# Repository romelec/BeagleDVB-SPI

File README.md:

BeagleDVB-SPI is a DVB-SPI interface on the BeagleBone Black to record/analyze TS streams.

This project is based on [BeagleLogic](https://github.com/abhishek-kakkar/BeagleLogic)

It uses the Programmable Real-Time units and matching firmware and Linux kernel modules on the
BeagleBone Black.

This is a work in progress, it kinda works but misses some data.

Directories:

* firmware: PRU Firmware
* kernel: Device Tree overlay source and kernel module source and Makefile.
* cape: The cape design files done with KiCAD

* parsing: An application to get the data and parse it to have usable TS stream
2 parameters: in and out file, generally /dev/beagledvbspi and the ouput ts file

License
--------

 * **PRU firmware & Device tree overlay** : GPLv2
 * **Kernel Module**: GPLv2
 * **Cape** : CERN Open Hardware License

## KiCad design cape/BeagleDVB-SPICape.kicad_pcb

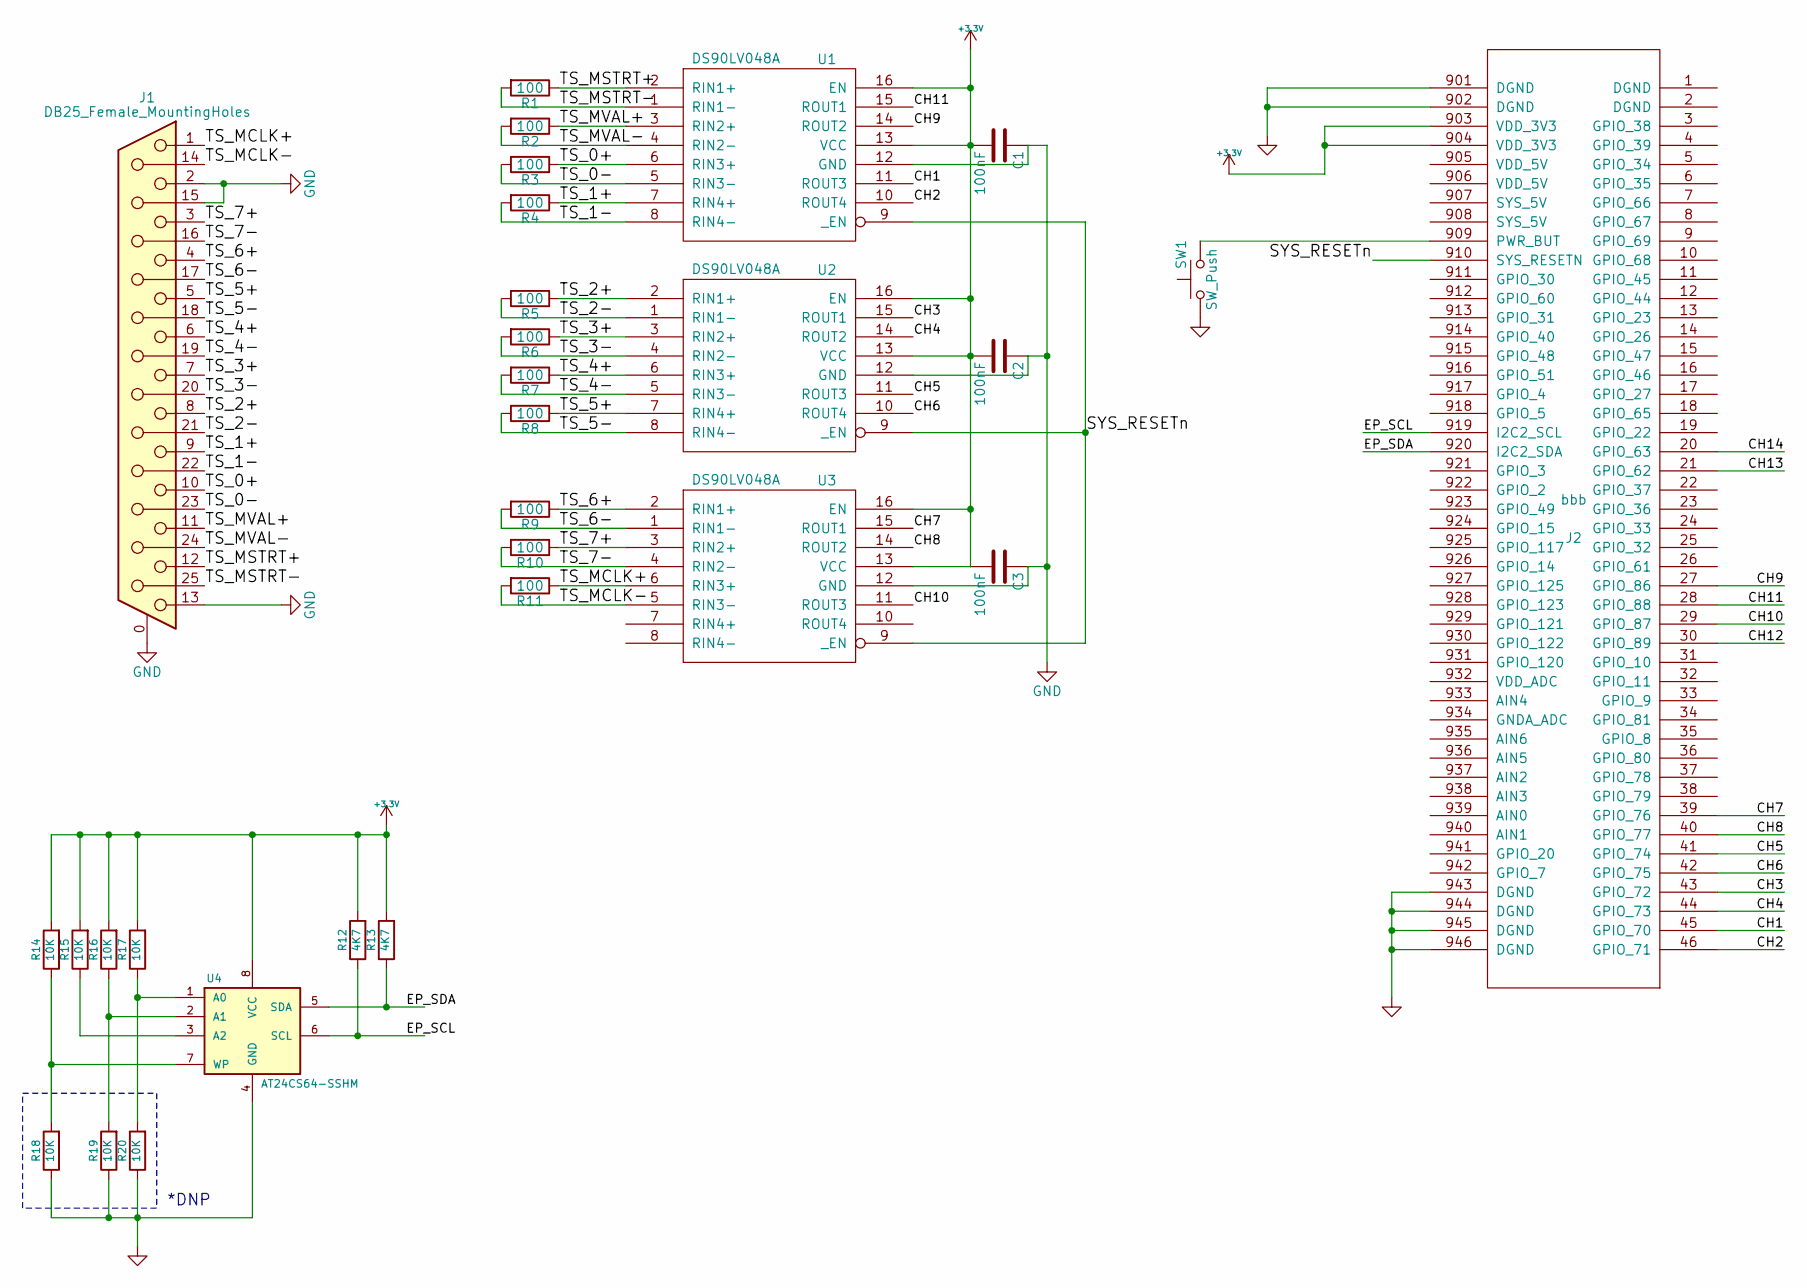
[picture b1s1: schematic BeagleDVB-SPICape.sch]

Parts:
C1, C2, C3: 100nF; C_0805
J1: DB25_Female_MountingHoles; DB25FC
J2: bbb; BBB
R1, R2, R3, R4, R5, R6, R7, R8, R9, R10, R11: 100; R_0603
R12, R13: 4K7; R_0603
R14, R15, R16, R17, R18, R19, R20: 10K; R_0603
SW1: SW_Push; SW_SPST_PTS645
U1, U2, U3: DS90LV048A; SOIC-16W_5.3x10.2mm_Pitch1.27mm
U4: AT24CS64-SSHM; SOIC-8_3.9x4.9mm_Pitch1.27mm

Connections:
+3V3: C1.2, C2.2, C3.2, J2.903 (VDD_3V3), J2.904 (VDD_3V3), R12.2, R13.2, R14.2, R15.2, R16.2, R17.2, U1.13 (VCC), U1.16 (EN), U2.13 (VCC), U2.16 (EN), U3.13 (VCC), U3.16 (EN), U4.8 (VCC)
/CH1: J2.45 (GPIO_70), U1.11 (ROUT3)
/CH2: J2.46 (GPIO_71), U1.10 (ROUT4)
/CH3: J2.43 (GPIO_72), U2.15 (ROUT1)
/CH4: J2.44 (GPIO_73), U2.14 (ROUT2)
/CH5: J2.41 (GPIO_74), U2.11 (ROUT3)
/CH6: J2.42 (GPIO_75), U2.10 (ROUT4)
/CH7: J2.39 (GPIO_76), U3.15 (ROUT1)
/CH8: J2.40 (GPIO_77), U3.14 (ROUT2)
/CH9: J2.27 (GPIO_86), U1.14 (ROUT2)
/CH10: J2.29 (GPIO_87), U3.11 (ROUT3)
/CH11: J2.28 (GPIO_88), U1.15 (ROUT1)
/CH12: J2.30 (GPIO_89)
/CH13: J2.21 (GPIO_62)
/CH14: J2.20 (GPIO_63)
/EP_SCL: J2.919 (I2C2_SCL), R12.1, U4.6 (SCL)
/EP_SDA: J2.920 (I2C2_SDA), R13.1, U4.5 (SDA)
/SYS_RESETn: J2.910 (SYS_RESETN), U1.9 (_EN), U2.9 (_EN), U3.9 (_EN)
/TS_0+: J1.10, R3.1, U1.6 (RIN3+)
/TS_0-: J1.23, R3.2, U1.5 (RIN3-)
/TS_1+: J1.9, R4.1, U1.7 (RIN4+)
/TS_1-: J1.22, R4.2, U1.8 (RIN4-)
/TS_2+: J1.8, R5.1, U2.2 (RIN1+)
/TS_2-: J1.21, R5.2, U2.1 (RIN1-)
/TS_3+: J1.7, R6.1, U2.3 (RIN2+)
/TS_3-: J1.20, R6.2, U2.4 (RIN2-)
/TS_4+: J1.6, R7.1, U2.6 (RIN3+)
/TS_4-: J1.19, R7.2, U2.5 (RIN3-)
/TS_5+: J1.5, R8.1, U2.7 (RIN4+)
/TS_5-: J1.18, R8.2, U2.8 (RIN4-)
/TS_6+: J1.4, R9.1, U3.2 (RIN1+)
/TS_6-: J1.17, R9.2, U3.1 (RIN1-)
/TS_7+: J1.3, R10.1, U3.3 (RIN2+)
/TS_7-: J1.16, R10.2, U3.4 (RIN2-)
/TS_MCLK+: J1.1, R11.1, U3.6 (RIN3+)
/TS_MCLK-: J1.14, R11.2, U3.5 (RIN3-)
/TS_MSTRT+: J1.12, R1.1, U1.2 (RIN1+)
/TS_MSTRT-: J1.25, R1.2, U1.1 (RIN1-)
/TS_MVAL+: J1.11, R2.1, U1.3 (RIN2+)
/TS_MVAL-: J1.24, R2.2, U1.4 (RIN2-)
GND: C1.1, C2.1, C3.1, J1.0 (PAD), J1.2, J1.13, J1.15, J2.901 (DGND), J2.902 (DGND), J2.943 (DGND), J2.944 (DGND), J2.945 (DGND), J2.946 (DGND), R18.1, R19.1, R20.1, SW1.1, U1.12 (GND), U2.12 (GND), U3.12 (GND), U4.4 (GND)
unnamed: J2.909 (PWR_BUT), SW1.2
unnamed: R14.1, R18.2, U4.7 (WP)
unnamed: R15.1, U4.3 (A2)
unnamed: R16.1, R19.2, U4.2 (A1)
unnamed: R17.1, R20.2, U4.1 (A0)

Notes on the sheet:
*DNP

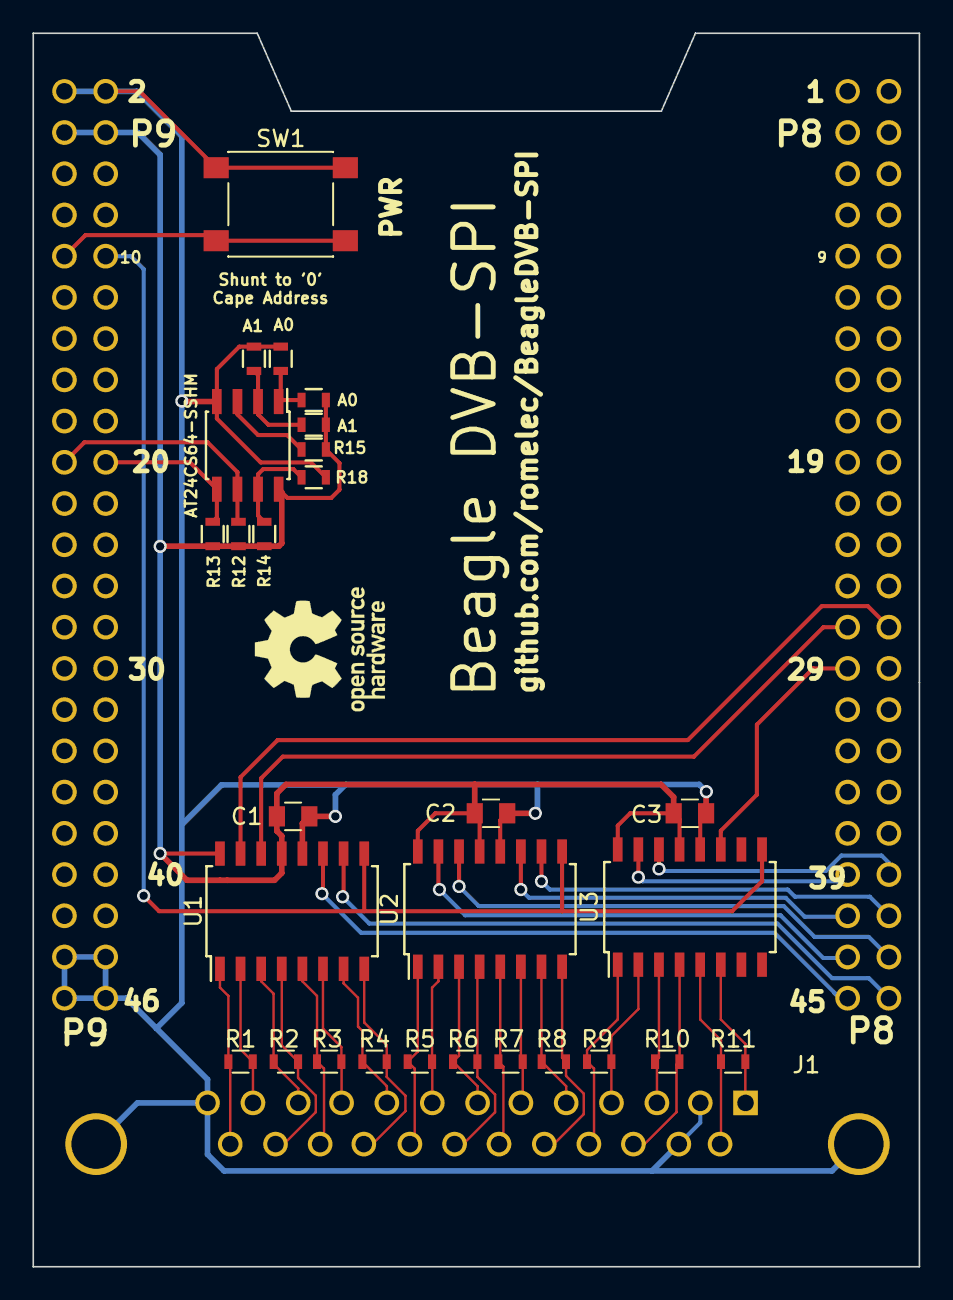
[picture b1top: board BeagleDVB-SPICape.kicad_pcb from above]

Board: 2 copper layers, 54.6 x 76.0 mm, 30 parts (1 on the bottom side), 43 nets.

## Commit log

2018-03-07 remove unused files
2018-03-07 clean cape
2018-03-07 add new cape
2018-03-07 update firmware
2018-03-07 update kernel
2018-03-07 update scripts and add parsing app
